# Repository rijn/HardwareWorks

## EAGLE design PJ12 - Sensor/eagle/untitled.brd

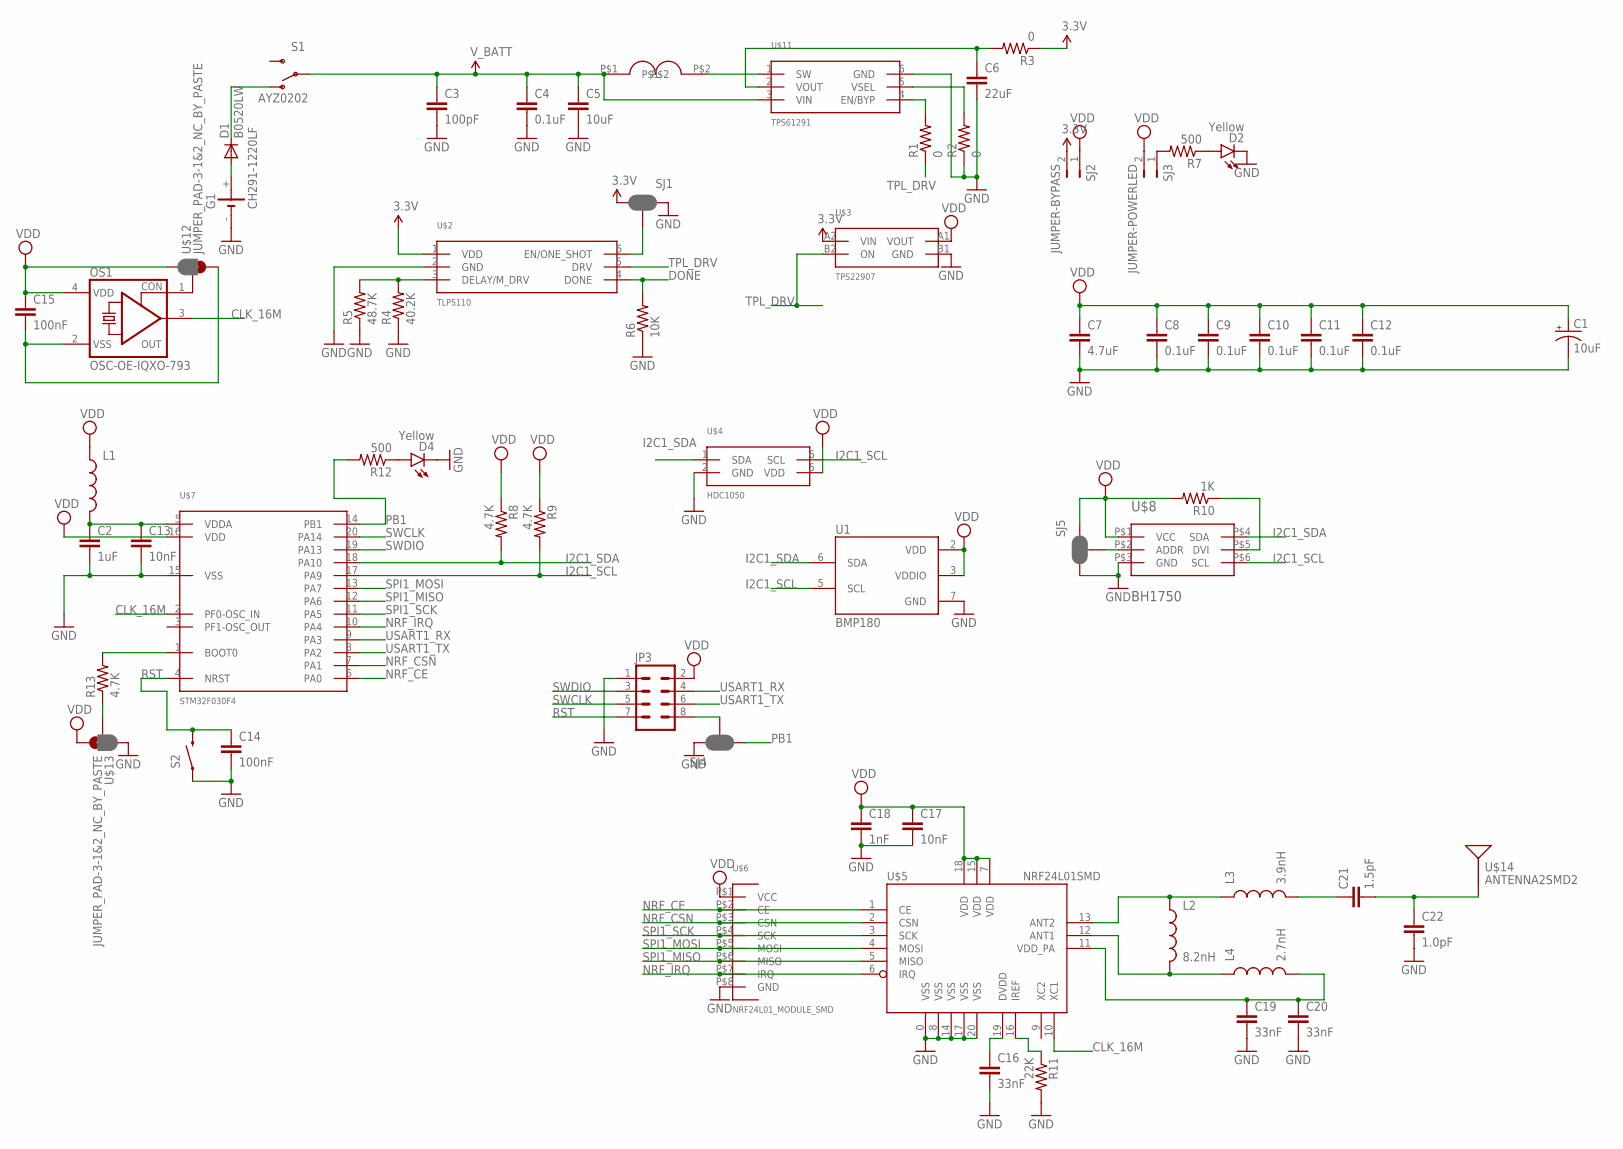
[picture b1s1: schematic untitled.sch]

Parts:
C1: 10uF; EIA3216
C2: 1uF; 0603-CAP
C3: 100pF; 0603-CAP
C4, C8, C9, C10, C11, C12: 0.1uF; 0603-CAP
C5: 10uF; 0603-CAP
C6: 22uF; 0603-CAP
C7: 4.7uF; 0603-CAP
C13, C17: 10nF; 0603-CAP
C14, C15: 100nF; 0603-CAP
C16, C19, C20: 33nF; 0603-CAP
C18: 1nF; 0603-CAP
C21: 1.5pF; 0603-CAP
C22: 1.0pF; 0603-CAP
D1: B0520LW; SOD-123_MINI-SMA
D2, D4: Yellow; LED-0603
G1: CH291-1220LF
JP3: M04X2SMD; 2X4_SMD
L1: INDUCTOR0603; 0603
L2: 8.2nH; 0603
L3: 3.9nH; 0603
L4: 2.7nH; 0603
OS1: OSC-OE-IQXO-793; 2.5X2-4-PAD
R1, R2, R3: 0; 0603
R4: 40.2K; 0805
R5: 48.7K; 0805
R6: 10K; 0603
R7, R12: 500; 0603
R8, R9, R13: 4.7K; 0603
R10: 1K; 0603
R11: 22K; 0603
S1: AYZ0202
S2: SWITCH-MOMENTARY-2SMD-REDUNDANT; TACTILE-SWITCH-SMD
SJ1, SJ4, SJ5: JUMPER-PAD-3-NC_BY_PASTE; PAD-JUMPER-3-NC_BY_PASTE_YES_SILK_FULL_BOX
SJ2: JUMPER-BYPASS; PTH-JUMPER-2-NO_NO_SILK
SJ3: JUMPER-POWERLED; PTH-JUMPER-2-NO_NO_SILK
U1: BMP180
U$1: SWPA4018S3R3MT; SWPA4018S
U$2: TLP5110; DDC(R-PDSO-G6)
U$3: TPS22907; YZT(S-XBGA-N4)
U$4: HDC1050; DMB(S-PWSON-N6)
U$5: NRF24L01SMD; QFN20
U$6: NRF24L01_MODULE_SMD; M08-1.27
U$7: STM32F030F4; TSSOP20
U$8: BH1750; WSOF-6
U$11: TPS61291; DRV(S-PWSON-N6)
U$12, U$13: JUMPER_PAD-3-1&2_NC_BY_PASTE; PAD-HUMPER-3-1&2_NC_BY_PASTE_YES_SILK_FULL_BOX
U$14: ANTENNA2SMD2; ANTENNA-CHIP3

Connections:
3.3V: R3.1, SJ1.1, SJ2.2, U$2.1 (VDD), U$3.A2 (VIN)
CLK_16M: OS1.3 (OUT), U$5.10 (XC1), U$7.2 (PF0-OSC_IN)
DONE: R6.2, U$2.4 (DONE)
GND: C1.C (-), C2.2, C3.2, C4.2, C5.2, C6.2, C7.2, C8.2, C9.2, C10.2, C11.2, C12.2, C13.2, C14.2, C16.2, C17.2, C18.2, C19.2, C20.2, C22.2, D2.C, D4.C, G1.-, JP3.1, R2.1, R4.1, R5.1, R6.1, R11.2, S2.1, S2.2 (1), SJ1.3, SJ4.3, SJ5.1, U1.7 (GND), U$2.2 (GND), U$3.B1 (GND), U$4.2 (GND), U$5.0 (VSS), U$5.8 (VSS), U$5.14 (VSS), U$5.17 (VSS), U$5.20 (VSS), U$6.P$8 (GND), U$7.15 (VSS), U$8.P$3 (GND), U$11.6 (GND), U$13.1
I2C1_SCL: R9.2, U1.5 (SCL), U$4.6 (SCL), U$7.17 (PA9), U$8.P$6 (SCL)
I2C1_SDA: R8.2, U1.6 (SDA), U$4.1 (SDA), U$7.18 (PA10), U$8.P$4 (SDA)
MESH: C1.A (+), C7.1, C8.1, C9.1, C10.1, C11.1, C12.1, R8.1, R9.1, R10.2, SJ2.1, SJ3.2, SJ5.3, U1.2 (VDD), U1.3 (VDDIO), U$6.P$1 (VCC), U$8.P$1 (VCC)
unnamed: D1.A, G1.+
unnamed: D1.C, S1.1 (O)
unnamed: U$1.P$2, U$11.1 (SW)
unnamed: C6.1, R3.2, U$11.2 (VOUT)
unnamed: R1.2, U$11.4 (EN/BYP)
unnamed: R2.2, U$11.5 (VSEL)
unnamed: R4.2, R5.2, U$2.3 (DELAY/M_DRV)
unnamed: R7.2, SJ3.1
unnamed: D2.A, R7.1
unnamed: SJ1.2, U$2.6 (EN/ONE_SHOT)
unnamed: L2.1, L3.1, U$5.13 (ANT2)
unnamed: SJ5.2, U$8.P$2 (ADDR)
unnamed: R10.1, U$8.P$5 (DVI)
unnamed: L2.2, L4.1, U$5.12 (ANT1)
unnamed: D4.A, R12.1
unnamed: C15.2, OS1.2 (VSS), U$12.3
unnamed: C2.1, C13.1, L1.2, U$7.5 (VDDA)
unnamed: C19.1, C20.1, L4.2, U$5.11 (VDD_PA)
unnamed: R13.1, U$13.2
unnamed: JP3.8, SJ4.2
unnamed: R13.2, U$7.1 (BOOT0)
unnamed: OS1.1 (CON), U$12.2
unnamed: C16.1, U$5.19 (DVDD)
unnamed: R11.1, U$5.16 (IREF)
unnamed: C21.1, L3.2
unnamed: C21.2, C22.1, U$14.FEED
NRF_CE: U$5.1 (CE), U$6.P$2 (CE), U$7.6 (PA0)
NRF_CSN: U$5.2 (CSN), U$6.P$3 (CSN), U$7.7 (PA1)
NRF_IRQ: U$5.6 (IRQ), U$6.P$7 (IRQ), U$7.10 (PA4)
PB1: R12.2, SJ4.1, U$7.14 (PB1)
RST: C14.1, JP3.7, S2.3 (2), S2.4 (2), U$7.4 (NRST)
SPI1_MISO: U$5.5 (MISO), U$6.P$6 (MISO), U$7.12 (PA6)
SPI1_MOSI: U$5.4 (MOSI), U$6.P$5 (MOSI), U$7.13 (PA7)
SPI1_SCK: U$5.3 (SCK), U$6.P$4 (SCK), U$7.11 (PA5)
SWCLK: JP3.5, U$7.20 (PA14)
SWDIO: JP3.3, U$7.19 (PA13)
TPL_DRV: R1.1, U$2.5 (DRV), U$3.B2 (ON)
USART1_RX: JP3.4, U$7.9 (PA3)
USART1_TX: JP3.6, U$7.8 (PA2)
VDD: C15.1, C17.1, C18.1, JP3.2, L1.1, OS1.4 (VDD), U$3.A1 (VOUT), U$4.5 (VDD), U$5.7 (VDD), U$5.15 (VDD), U$5.18 (VDD), U$7.16 (VDD), U$12.1, U$13.3
V_BATT: C3.1, C4.1, C5.1, S1.2, U$1.P$1, U$11.3 (VIN)

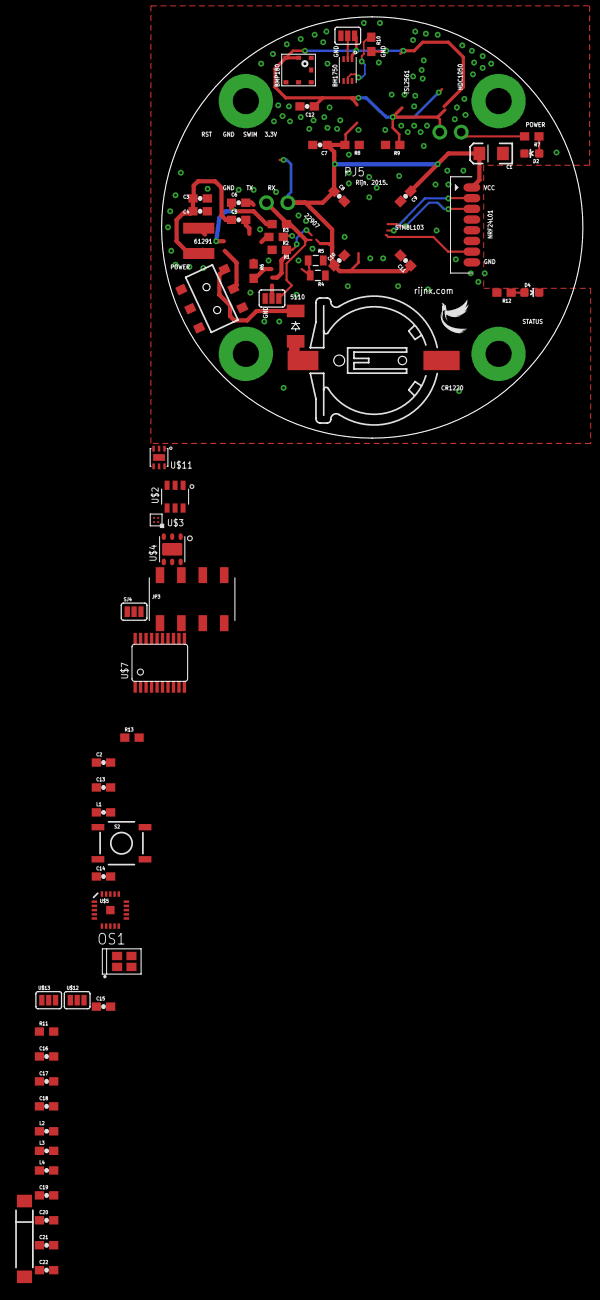
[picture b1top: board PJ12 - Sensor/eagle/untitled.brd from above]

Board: 2 copper layers, 50.0 x 50.0 mm, 67 parts (1 on the bottom side), 48 nets.

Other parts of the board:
U$9: LOGO-3
U$10: LOGO-1

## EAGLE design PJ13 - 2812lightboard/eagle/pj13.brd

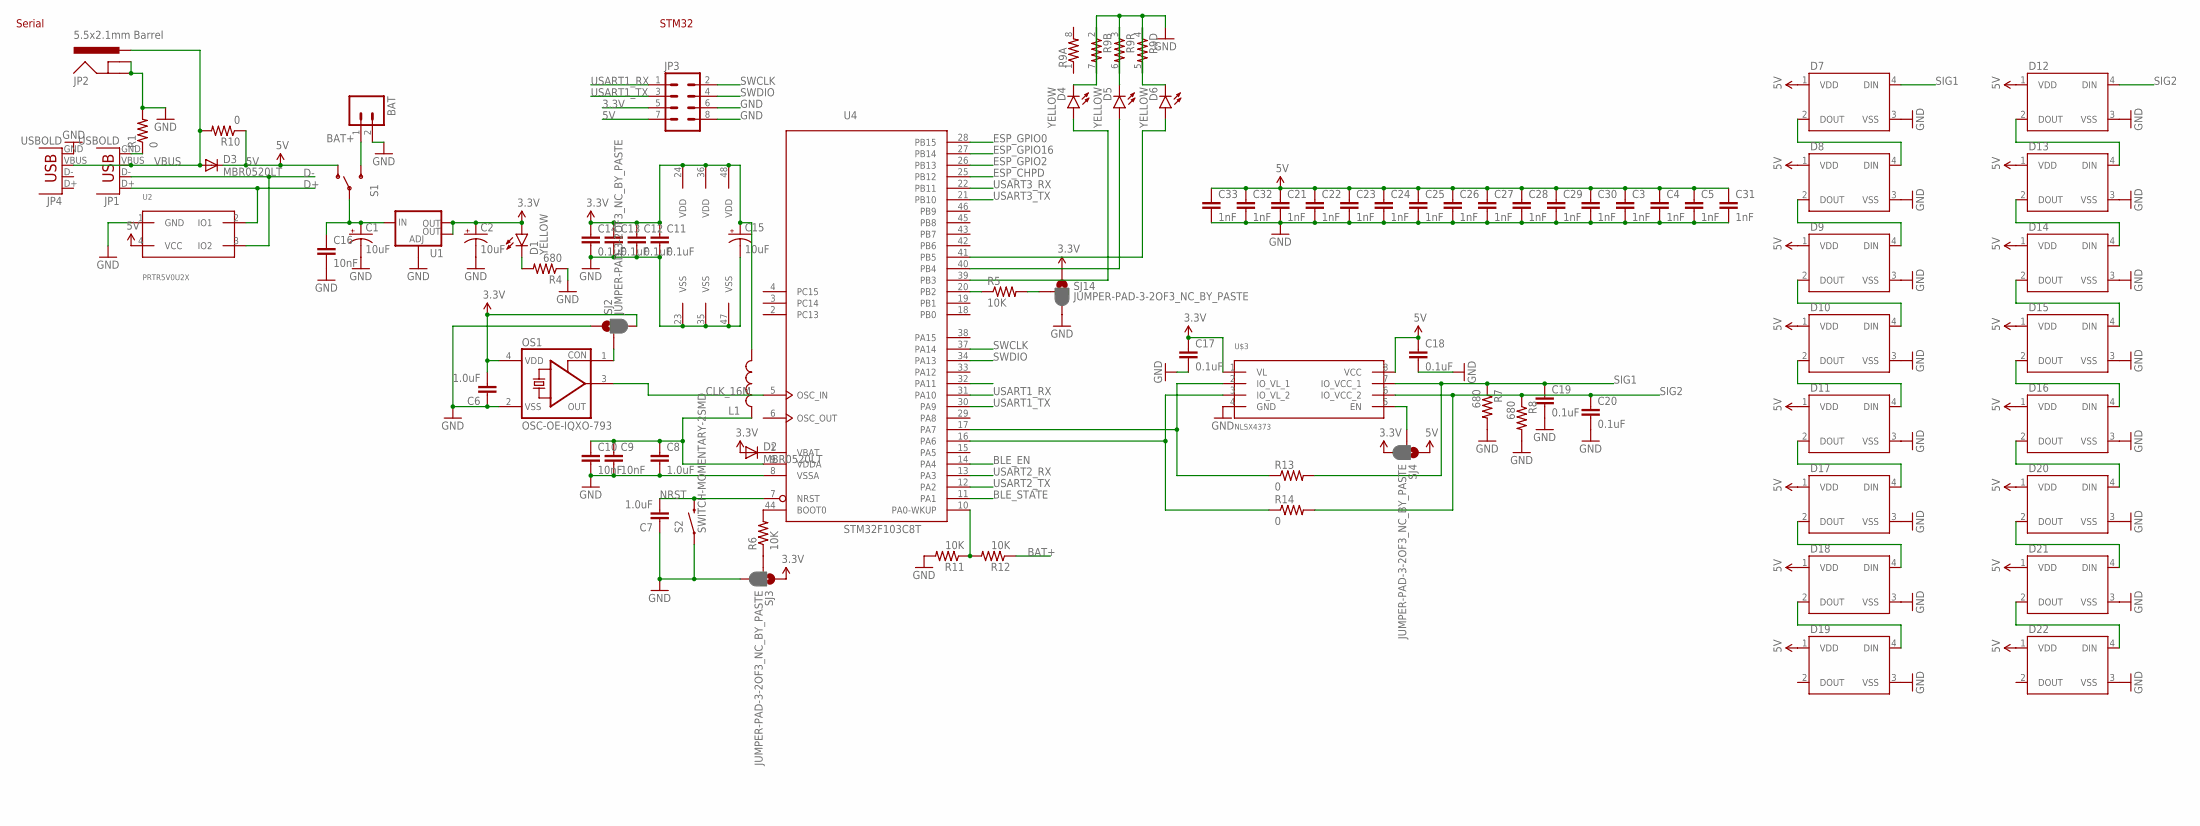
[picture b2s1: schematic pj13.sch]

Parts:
BAT: M02LOCK; 1X02_LOCK
C1, C2, C15: 10uF; EIA3216
C3, C4, C5, C21, C22, C23, C24, C25, C26, C27, C28, C29, C30, C31, C32, C33: 1nF; 0603-CAP
C6, C7, C8: 1.0uF; 0603-CAP
C9, C10, C16: 10nF; 0603-CAP
C11, C12, C13, C14, C17, C18, C19, C20: 0.1uF; 0603-CAP
D1, D4, D5, D6: YELLOW; LED-1206
D2, D3: MBR0520LT; SOD123
D7, D8, D9, D10, D11, D12, D13, D14, D15, D16, D17, D18, D19, D20, D21, D22: WS2812B
JP1, JP4: USBOLD; USB-MINIB-OLD
JP2: 5.5x2.1mm Barrel; POWER_JACK_SMD
JP3: M04X2SMD; 2X4_SMD
L1: INDUCTOR0603; 0603
OS1: OSC-OE-IQXO-793; 2.5X2-4-PAD
R1, R10: 0; 0603
R4, R7, R8: 680; 0603-RES
R5, R6, R11, R12: 10K; 0603-RES
R9: RESISTOR-ARRAY0603-ARV; 0603-ARV
R13, R14: 0; 0603-RES
S1: SWITCH-SPDTSMD; AYZ0202
S2: SWITCH-MOMENTARY-2SMD; TACTILE-SWITCH-SMD
SJ2, SJ3, SJ4, SJ14: JUMPER-PAD-3-2OF3_NC_BY_PASTE; PAD-JUMPER-3-2OF3_NC_BY_PASTE_YES_SILK_FULL_BOX
U1: V_REG_LM1117SOT223; SOT223
U2: PRTR5V0U2X; SOT143
U4: STM32F103C8T; LQFP48
U$3: NLSX4373; SO08

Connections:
3.3V: C2.A (+), C6.2, C11.1, C12.1, C13.1, C14.1, C15.A (+), C17.1, D1.A, D2.A, JP3.5, L1.2, OS1.4 (VDD), SJ2.3, SJ3.1, SJ4.3, SJ14.1, U1.2 (OUT), U1.4 (OUT), U4.24 (VDD), U4.36 (VDD), U4.48 (VDD), U$3.1 (VL)
5V: C3.1, C4.1, C5.1, C18.1, C21.1, C22.1, C23.1, C24.1, C25.1, C26.1, C27.1, C28.1, C29.1, C30.1, C31.1, C32.1, C33.1, D3.C, D7.1 (VDD), D8.1 (VDD), D9.1 (VDD), D10.1 (VDD), D11.1 (VDD), D12.1 (VDD), D13.1 (VDD), D14.1 (VDD), D15.1 (VDD), D16.1 (VDD), D17.1 (VDD), D18.1 (VDD), D19.1 (VDD), D20.1 (VDD), D21.1 (VDD), D22.1 (VDD), JP3.7, R10.1, S1.1 (O), SJ4.1, U2.4 (VCC), U$3.8 (VCC)
BAT+: BAT.1, R12.1, S1.3 (S)
BLE_EN: U4.14 (PA4)
BLE_STATE: U4.11 (PA1)
CLK_16M: OS1.3 (OUT), U4.5 (OSC_IN)
D+: JP1.D+, U2.2 (IO1)
D-: JP1.D-, U2.3 (IO2)
ESP_CHPD: U4.25 (PB12)
ESP_GPIO0: U4.28 (PB15)
ESP_GPIO2: U4.26 (PB13)
ESP_GPIO16: U4.27 (PB14)
GND: BAT.2, C1.C (-), C2.C (-), C3.2, C4.2, C5.2, C6.1, C7.1, C8.2, C9.2, C10.2, C11.2, C12.2, C13.2, C14.2, C15.C (-), C16.2, C17.2, C18.2, C19.2, C20.2, C21.2, C22.2, C23.2, C24.2, C25.2, C26.2, C27.2, C28.2, C29.2, C30.2, C31.2, C32.2, C33.2, D7.3 (VSS), D8.3 (VSS), D9.3 (VSS), D10.3 (VSS), D11.3 (VSS), D12.3 (VSS), D13.3 (VSS), D14.3 (VSS), D15.3 (VSS), D16.3 (VSS), D17.3 (VSS), D18.3 (VSS), D19.3 (VSS), D20.3 (VSS), D21.3 (VSS), D22.3 (VSS), JP2.GND (GNDBREAK), JP2.P$4 (GND), JP3.6, JP3.8, JP4.GND, OS1.2 (VSS), R1.2, R4.1, R7.2, R8.2, R9.5 (2), R9.6 (2), R9.7 (2), R11.2, S2.1, SJ2.1, SJ3.3, SJ14.3, U1.1 (ADJ), U2.1 (GND), U4.8 (VSSA), U4.23 (VSS), U4.35 (VSS), U4.47 (VSS), U$3.4 (GND)
unnamed: JP1.GND, R1.1
unnamed: D11.2 (DOUT), D17.4 (DIN)
unnamed: D1.C, R4.2
unnamed: D2.C, U4.1 (VBAT)
unnamed: R11.1, R12.2, U4.10 (PA0-WKUP)
unnamed: C8.1, C9.1, C10.1, L1.1, U4.9 (VDDA)
unnamed: R6.2, U4.44 (BOOT0)
unnamed: D6.A, U4.41 (PB5)
unnamed: R6.1, SJ3.2
unnamed: D17.2 (DOUT), D18.4 (DIN)
unnamed: OS1.1 (CON), SJ2.2
unnamed: D5.A, U4.40 (PB4)
unnamed: SJ4.2, U$3.5 (EN)
unnamed: D18.2 (DOUT), D19.4 (DIN)
unnamed: D4.A, U4.39 (PB3)
unnamed: D4.C, R9.2 (1)
unnamed: D5.C, R9.3 (1)
unnamed: D6.C, R9.4 (1)
unnamed: C1.A (+), C16.1, S1.2, U1.3 (IN)
unnamed: D12.2 (DOUT), D13.4 (DIN)
unnamed: D13.2 (DOUT), D14.4 (DIN)
unnamed: R13.1, U4.17 (PA7), U$3.2 (IO_VL_1)
unnamed: R14.1, U4.16 (PA6), U$3.3 (IO_VL_2)
unnamed: D7.2 (DOUT), D8.4 (DIN)
unnamed: D8.2 (DOUT), D9.4 (DIN)
unnamed: D9.2 (DOUT), D10.4 (DIN)
unnamed: D10.2 (DOUT), D11.4 (DIN)
unnamed: D14.2 (DOUT), D15.4 (DIN)
unnamed: D15.2 (DOUT), D16.4 (DIN)
unnamed: D16.2 (DOUT), D20.4 (DIN)
unnamed: D20.2 (DOUT), D21.4 (DIN)
unnamed: D21.2 (DOUT), D22.4 (DIN)
unnamed: R5.2, SJ14.2
NRF_CSN: U4.32 (PA11)
NRST: C7.2, S2.3 (2), U4.7 (NRST)
OURET: R5.1, U4.20 (PB2)
SIG1: C19.1, D7.4 (DIN), R7.1, R13.2, U$3.7 (IO_VCC_1)
SIG2: C20.1, D12.4 (DIN), R8.1, R14.2, U$3.6 (IO_VCC_2)
SWCLK: JP3.2, U4.37 (PA14)
SWDIO: JP3.4, U4.34 (PA13)
USART1_RX: JP3.1, U4.31 (PA10)
USART1_TX: JP3.3, U4.30 (PA9)
USART2_RX: U4.13 (PA3)
USART2_TX: U4.12 (PA2)
USART3_RX: U4.22 (PB11)
USART3_TX: U4.21 (PB10)
VBUS: D3.A, JP1.VBUS, JP2.VIN0 (PWR), JP4.VBUS, R10.2

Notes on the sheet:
STM32
Serial

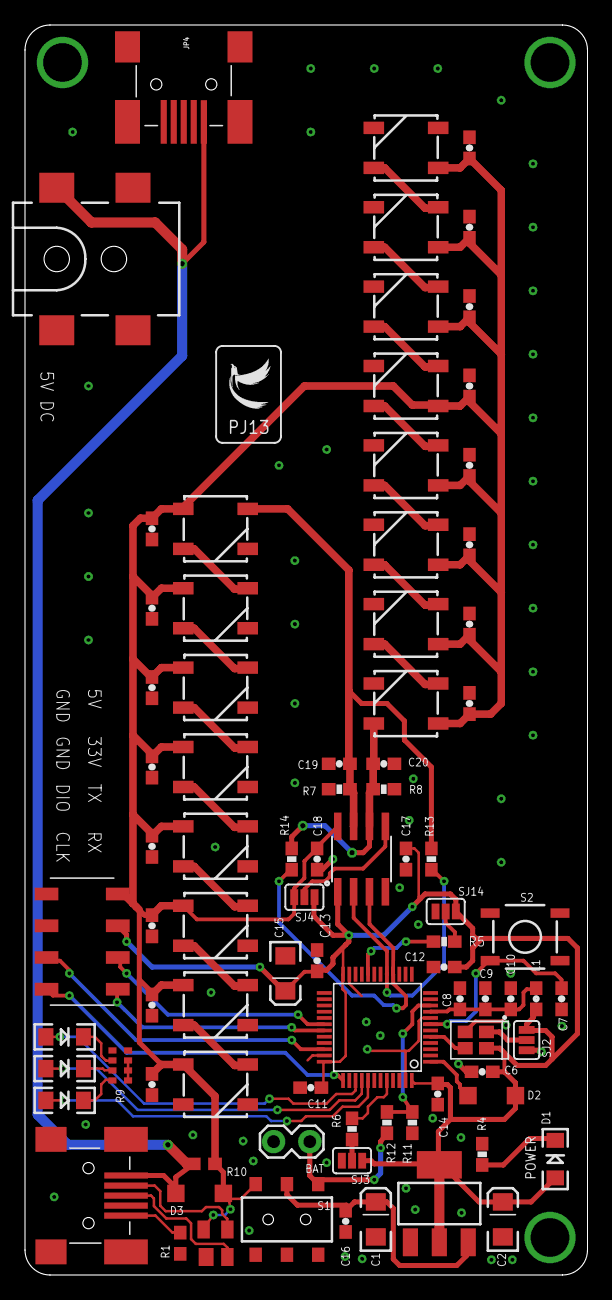
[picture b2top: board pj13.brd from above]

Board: 2 copper layers, 45.0 x 100.0 mm, 86 parts (1 on the bottom side), 49 nets.

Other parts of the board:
U$1: LOGO
U$2: ESD_10.00

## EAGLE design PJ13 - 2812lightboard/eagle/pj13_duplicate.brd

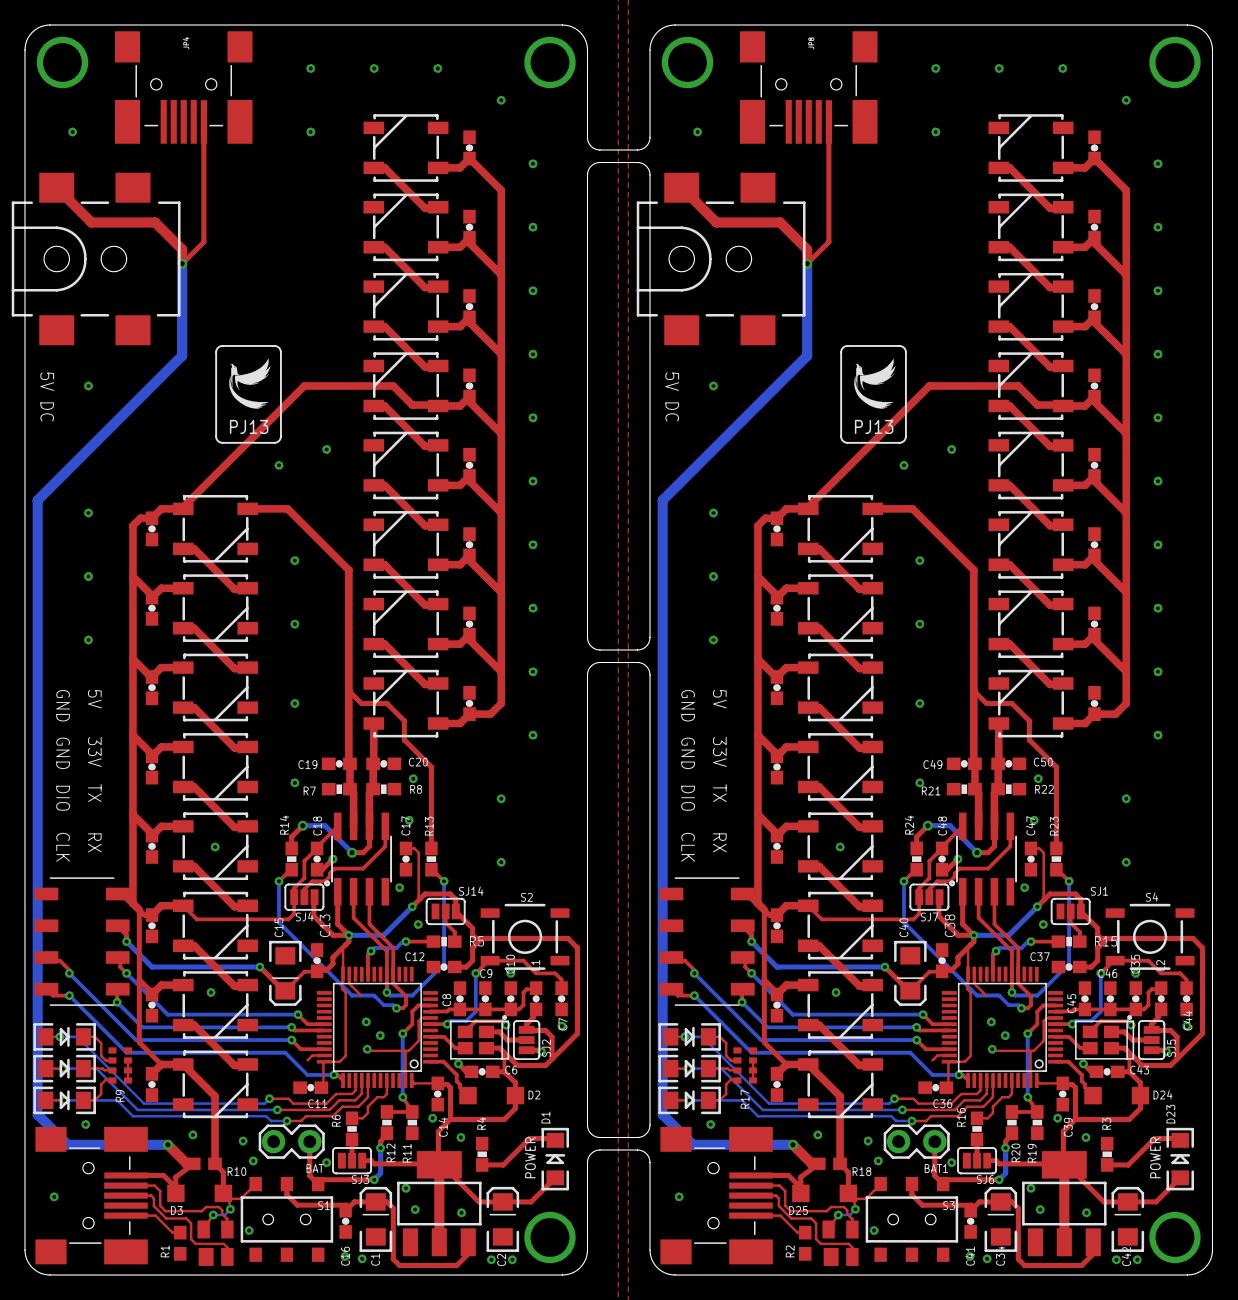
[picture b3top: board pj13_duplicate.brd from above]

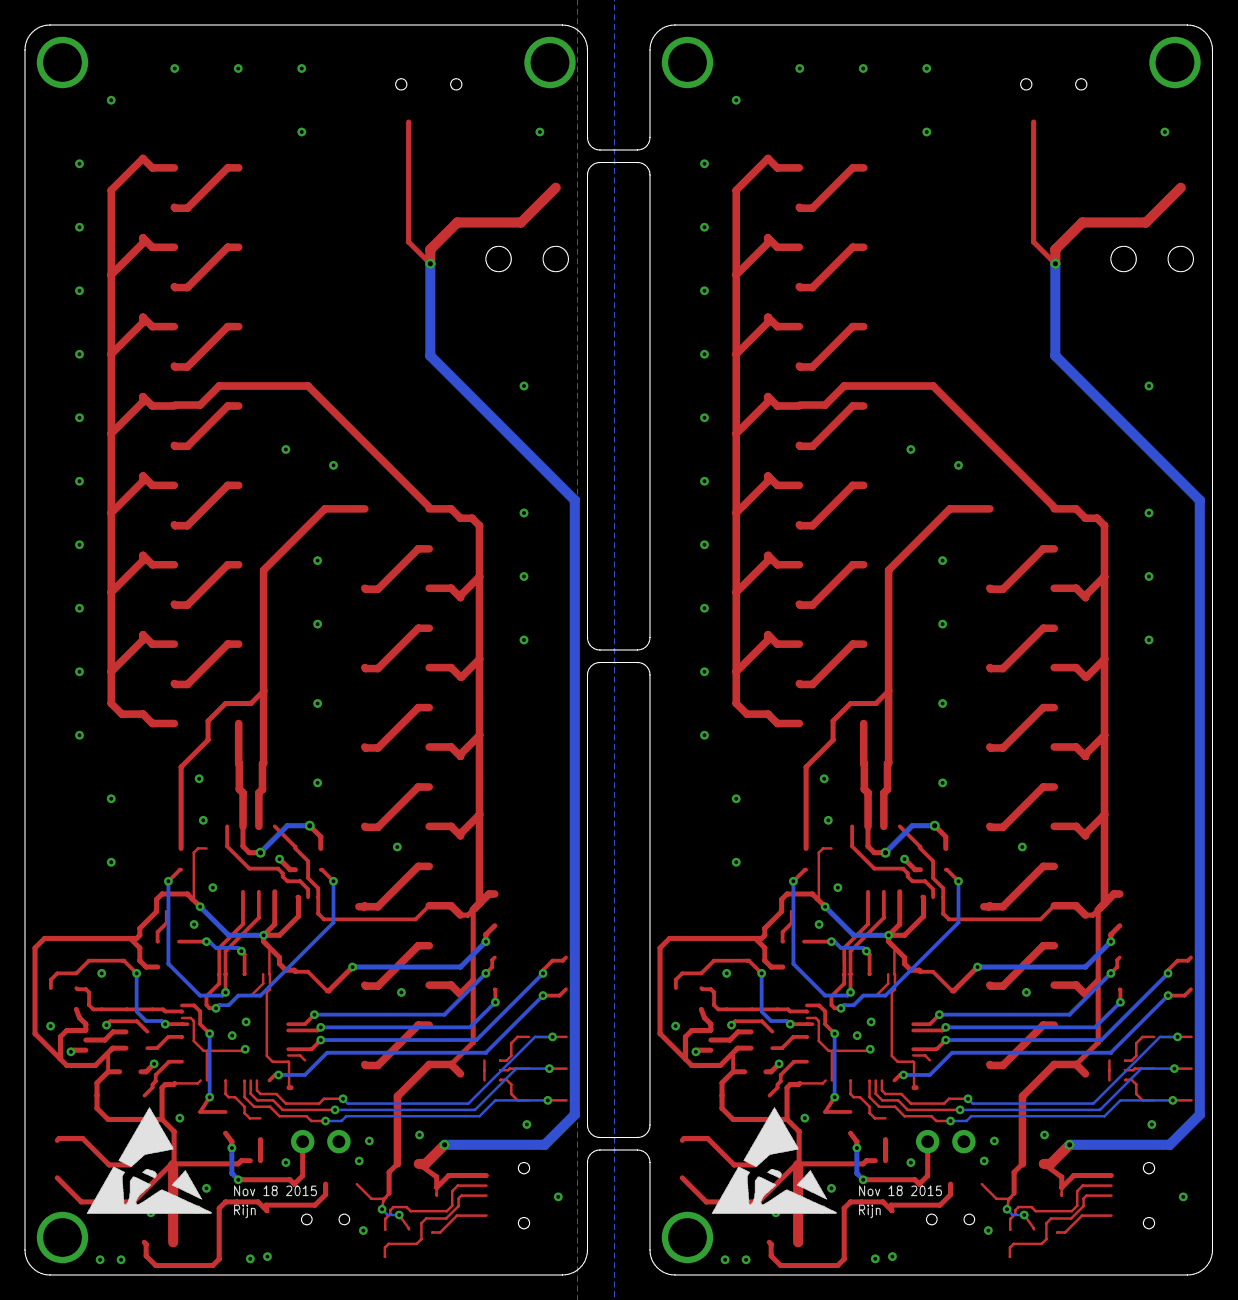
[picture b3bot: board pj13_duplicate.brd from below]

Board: 2 copper layers, 95.0 x 100.0 mm, 172 parts (2 on the bottom side), 98 nets.

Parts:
BAT, BAT1: 1X02_LOCK
C1, C2, C15, C34, C40, C42: 10uF; EIA3216
C3, C4, C5, C21, C22, C23, C24, C25, C26, C27, C28, C29, C30, C31, C32, C33, C51, C52, C53, C54, C55, C56, C57, C58, C59, C60, C61, C62, C63, C64, C65, C66: 1nF; 0603-CAP
C6, C7, C8, C43, C44, C45: 1.0uF; 0603-CAP
C9, C10, C16, C35, C41, C46: 10nF; 0603-CAP
C11, C12, C13, C14, C17, C18, C19, C20, C36, C37, C38, C39, C47, C48, C49, C50: 0.1uF; 0603-CAP
D1, D4, D5, D6, D23, D26, D27, D28: YELLOW; LED-1206
D2, D3, D24, D25: MBR0520LT; SOD123
D7, D8, D9, D10, D11, D12, D13, D14, D15, D16, D17, D18, D19, D20, D21, D22, D29, D30, D31, D32, D33, D34, D35, D36, D37, D38, D39, D40, D41, D42, D43, D44: WS2812B
JP1, JP4, JP5, JP8: USBOLD; USB-MINIB-OLD
JP2, JP7: 5.5x2.1mm Barrel; POWER_JACK_SMD
JP3, JP6: 2X4_SMD
L1, L2: 0603
OS1, OS2: OSC-OE-IQXO-793; 2.5X2-4-PAD
R1, R2, R10, R18: 0; 0603
R3, R4, R7, R8, R21, R22: 680; 0603-RES
R5, R6, R11, R12, R15, R16, R19, R20: 10K; 0603-RES
R9, R17: 0603-ARV
R13, R14, R23, R24: 0; 0603-RES
S1, S3: AYZ0202
S2, S4: SWITCH-MOMENTARY-2SMD; TACTILE-SWITCH-SMD
SJ1, SJ2, SJ3, SJ4, SJ5, SJ6, SJ7, SJ14: JUMPER-PAD-3-2OF3_NC_BY_PASTE; PAD-JUMPER-3-2OF3_NC_BY_PASTE_YES_SILK_FULL_BOX
U1, U3: SOT223
U2, U5: PRTR5V0U2X; SOT143
U4, U6: STM32F103C8T; LQFP48
U$1, U$4: LOGO
U$2, U$5: ESD_10.00
U$3, U$6: NLSX4373; SO08

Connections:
3.3V: C2.A, C6.2, C11.1, C12.1, C13.1, C14.1, C15.A, C17.1, D1.A, D2.A, JP3.5, L1.2, OS1.4, SJ2.3, SJ3.1, SJ4.3, SJ14.1, U1.2, U1.4, U4.24, U4.36, U4.48, U$3.1
3.3V1: C36.1, C37.1, C38.1, C39.1, C40.A, C42.A, C43.2, C47.1, D23.A, D24.A, JP6.5, L2.2, OS2.4, SJ1.1, SJ5.3, SJ6.1, SJ7.3, U3.2, U3.4, U6.24, U6.36, U6.48, U$6.1
5V: C3.1, C4.1, C5.1, C18.1, C21.1, C22.1, C23.1, C24.1, C25.1, C26.1, C27.1, C28.1, C29.1, C30.1, C31.1, C32.1, C33.1, D3.C, D7.1, D8.1, D9.1, D10.1, D11.1, D12.1, D13.1, D14.1, D15.1, D16.1, D17.1, D18.1, D19.1, D20.1, D21.1, D22.1, JP3.7, R10.1, S1.1, SJ4.1, U2.4, U$3.8
5V1: C48.1, C51.1, C52.1, C53.1, C54.1, C55.1, C56.1, C57.1, C58.1, C59.1, C60.1, C61.1, C62.1, C63.1, C64.1, C65.1, C66.1, D25.C, D29.1, D30.1, D31.1, D32.1, D33.1, D34.1, D35.1, D36.1, D37.1, D38.1, D39.1, D40.1, D41.1, D42.1, D43.1, D44.1, JP6.7, R18.1, S3.1, SJ7.1, U5.4, U$6.8
BAT+: BAT.1, R12.1, S1.3
BAT+1: BAT1.1, R20.1, S3.3
CLK_16M: OS1.3, U4.5
CLK_16M1: OS2.3, U6.5
D+: JP1.D+, U2.2
D+1: JP5.D+, U5.2
D-: JP1.D-, U2.3
D-1: JP5.D-, U5.3
GND: BAT.2, C1.C, C2.C, C3.2, C4.2, C5.2, C6.1, C7.1, C8.2, C9.2, C10.2, C11.2, C12.2, C13.2, C14.2, C15.C, C16.2, C17.2, C18.2, C19.2, C20.2, C21.2, C22.2, C23.2, C24.2, C25.2, C26.2, C27.2, C28.2, C29.2, C30.2, C31.2, C32.2, C33.2, D7.3, D8.3, D9.3, D10.3, D11.3, D12.3, D13.3, D14.3, D15.3, D16.3, D17.3, D18.3, D19.3, D20.3, D21.3, D22.3, JP2.GND, JP2.P$4, JP3.6, JP3.8, JP4.GND, OS1.2, R1.2, R4.1, R7.2, R8.2, R9.5, R9.6, R9.7, R11.2, S2.1, SJ2.1, SJ3.3, SJ14.3, U1.1, U2.1, U4.8, U4.23, U4.35, U4.47, U$3.4
GND1: BAT1.2, C34.C, C35.2, C36.2, C37.2, C38.2, C39.2, C40.C, C41.2, C42.C, C43.1, C44.1, C45.2, C46.2, C47.2, C48.2, C49.2, C50.2, C51.2, C52.2, C53.2, C54.2, C55.2, C56.2, C57.2, C58.2, C59.2, C60.2, C61.2, C62.2, C63.2, C64.2, C65.2, C66.2, D29.3, D30.3, D31.3, D32.3, D33.3, D34.3, D35.3, D36.3, D37.3, D38.3, D39.3, D40.3, D41.3, D42.3, D43.3, D44.3, JP6.6, JP6.8, JP7.GND, JP7.P$4, JP8.GND, OS2.2, R2.2, R3.1, R17.5, R17.6, R17.7, R19.2, R21.2, R22.2, S4.1, SJ1.3, SJ5.1, SJ6.3, U3.1, U5.1, U6.8, U6.23, U6.35, U6.47, U$6.4
unnamed: JP1.GND, R1.1
unnamed: D11.2, D17.4
unnamed: D1.C, R4.2
unnamed: D2.C, U4.1
unnamed: R11.1, R12.2, U4.10
unnamed: C8.1, C9.1, C10.1, L1.1, U4.9
unnamed: R6.2, U4.44
unnamed: D6.A, U4.41
unnamed: R6.1, SJ3.2
unnamed: D17.2, D18.4
unnamed: OS1.1, SJ2.2
unnamed: D5.A, U4.40
unnamed: SJ4.2, U$3.5
unnamed: D18.2, D19.4
unnamed: D4.A, U4.39
unnamed: D4.C, R9.2
unnamed: D5.C, R9.3
unnamed: D6.C, R9.4
unnamed: C1.A, C16.1, S1.2, U1.3
unnamed: D12.2, D13.4
unnamed: D13.2, D14.4
unnamed: R13.1, U4.17, U$3.2
unnamed: R14.1, U4.16, U$3.3
unnamed: D7.2, D8.4
unnamed: D8.2, D9.4
unnamed: D9.2, D10.4
unnamed: D10.2, D11.4
unnamed: D14.2, D15.4
unnamed: D15.2, D16.4
unnamed: D16.2, D20.4
unnamed: D20.2, D21.4
unnamed: D21.2, D22.4
unnamed: JP5.GND, R2.1
unnamed: D23.C, R3.2
unnamed: R16.2, U6.44
unnamed: R16.1, SJ6.2
unnamed: OS2.1, SJ5.2
unnamed: C35.1, C45.1, C46.1, L2.1, U6.9
unnamed: D24.C, U6.1
unnamed: R15.2, SJ1.2
unnamed: D28.A, U6.41
unnamed: D27.A, U6.40
unnamed: D26.A, U6.39
unnamed: R5.2, SJ14.2
unnamed: D26.C, R17.2
unnamed: D27.C, R17.3
unnamed: D28.C, R17.4
unnamed: C34.A, C41.1, S3.2, U3.3
unnamed: R19.1, R20.2, U6.10
unnamed: SJ7.2, U$6.5
unnamed: R23.1, U6.17, U$6.2
unnamed: R24.1, U6.16, U$6.3
unnamed: D29.2, D30.4
unnamed: D30.2, D31.4
unnamed: D31.2, D32.4
unnamed: D32.2, D33.4
unnamed: D34.2, D35.4
unnamed: D35.2, D36.4
unnamed: D36.2, D37.4
unnamed: D37.2, D38.4
unnamed: D33.2, D39.4
unnamed: D39.2, D40.4
unnamed: D40.2, D41.4
unnamed: D38.2, D42.4
unnamed: D42.2, D43.4
unnamed: D43.2, D44.4
NRST: C7.2, S2.3, U4.7
NRST1: C44.2, S4.3, U6.7
OURET: R5.1, U4.20
OURET1: R15.1, U6.20
SIG1: C19.1, D7.4, R7.1, R13.2, U$3.7
SIG2: C20.1, D12.4, R8.1, R14.2, U$3.6
SIG3: C49.1, D29.4, R21.1, R23.2, U$6.7
SIG4: C50.1, D34.4, R22.1, R24.2, U$6.6
SWCLK: JP3.2, U4.37
SWCLK1: JP6.2, U6.37
SWDIO: JP3.4, U4.34
SWDIO1: JP6.4, U6.34
USART1_RX: JP3.1, U4.31
USART1_RX1: JP6.1, U6.31
USART1_TX: JP3.3, U4.30
USART1_TX1: JP6.3, U6.30
VBUS: D3.A, JP1.VBUS, JP2.VIN0, JP4.VBUS, R10.2
VBUS1: D25.A, JP5.VBUS, JP7.VIN0, JP8.VBUS, R18.2

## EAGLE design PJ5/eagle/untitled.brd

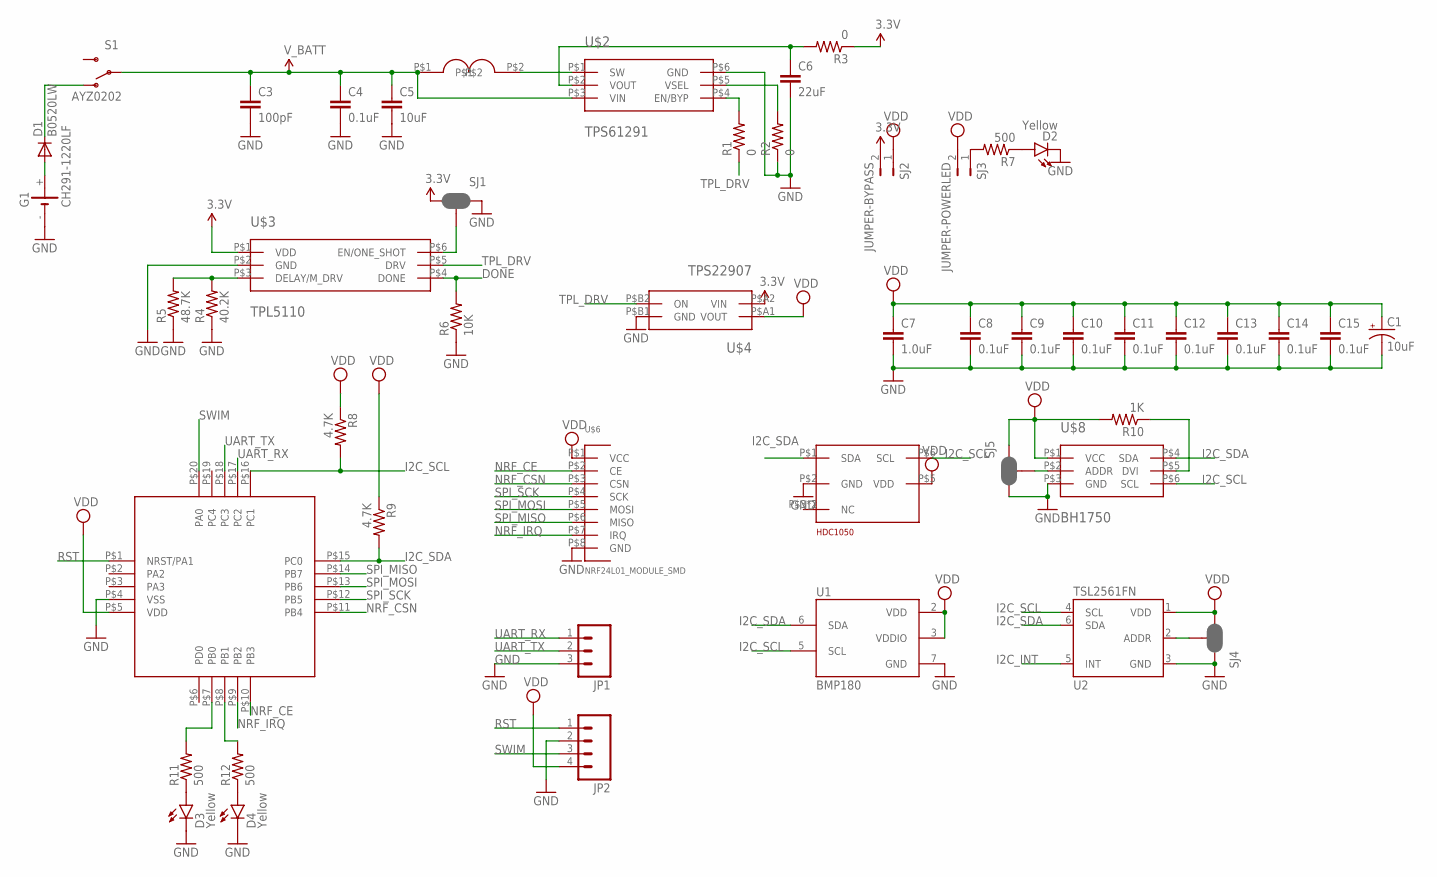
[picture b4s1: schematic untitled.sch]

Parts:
C1: 10uF; EIA3216
C3: 100pF; 0603-CAP
C4, C8, C9, C10, C11, C12, C13, C14, C15: 0.1uF; 0603-CAP
C5: 10uF; 0603-CAP
C6: 22uF; 0603-CAP
C7: 1.0uF; 0603-CAP
D1: B0520LW; SOD-123_MINI-SMA
D2, D3, D4: Yellow; LED-0603
G1: CH291-1220LF
JP1: M03LOCK; 1X03_LOCK
JP2: M04LOCK; 1X04_LOCK
R1, R2, R3: 0; 0603
R4: 40.2K; 0805
R5: 48.7K; 0805
R6: 10K; 0603
R7, R11, R12: 500; 0603
R8, R9: 4.7K; 0603
R10: 1K; 0603
S1: AYZ0202
SJ1, SJ4, SJ5: JUMPER-PAD-3-NC_BY_PASTE; PAD-JUMPER-3-NC_BY_PASTE_YES_SILK_FULL_BOX
SJ2: JUMPER-BYPASS; PTH-JUMPER-2-NO_NO_SILK
SJ3: JUMPER-POWERLED; PTH-JUMPER-2-NO_NO_SILK
U1: BMP180
U2: TSL2561FN; FN-6
U$1: SWPA4018S3R3MT; SWPA4018S
U$2: TPS61291; PWSON-N6
U$3: TPL5110; DDC(R-PDSO-G6)
U$4: TPS22907; YZT(S-XBGA-N4)
U$5: STM8L101; UFQFPN20
U$6: NRF24L01_MODULE_SMD; M08-1.27
U$7: HDC1050; PWSON-N6
U$8: BH1750; WSOF-6

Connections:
3.3V: R3.1, SJ1.1, SJ2.2, U$3.P$1 (VDD), U$4.P$A2 (VIN)
DONE: R6.2, U$3.P$4 (DONE)
GND: C1.C (-), C3.2, C4.2, C5.2, C6.2, C7.2, C8.2, C9.2, C10.2, C11.2, C12.2, C13.2, C14.2, C15.2, D2.C, D3.C, D4.C, G1.-, JP1.3, JP2.2, R2.1, R4.1, R5.1, R6.1, SJ1.3, SJ4.3, SJ5.1, U1.7 (GND), U2.3 (GND), U$2.P$6 (GND), U$3.P$2 (GND), U$4.P$B1 (GND), U$5.P$4 (VSS), U$6.P$8 (GND), U$7.P$2 (GND), U$8.P$3 (GND)
I2C_INT: U2.5 (INT)
I2C_SCL: R8.2, U1.5 (SCL), U2.4 (SCL), U$5.P$16 (PC1), U$7.P$6 (SCL), U$8.P$6 (SCL)
I2C_SDA: R9.2, U1.6 (SDA), U2.6 (SDA), U$5.P$15 (PC0), U$7.P$1 (SDA), U$8.P$4 (SDA)
MESH: C1.A (+), C7.1, C8.1, C9.1, C10.1, C11.1, C12.1, C13.1, C14.1, C15.1, JP2.4, R8.1, R9.1, R10.2, SJ2.1, SJ3.2, SJ4.1, SJ5.3, U1.2 (VDD), U1.3 (VDDIO), U2.1 (VDD), U$4.P$A1 (VOUT), U$5.P$5 (VDD), U$6.P$1 (VCC), U$7.P$5 (VDD), U$8.P$1 (VCC)
unnamed: D1.A, G1.+
unnamed: D1.C, S1.1 (O)
unnamed: U$1.P$2, U$2.P$1 (SW)
unnamed: C6.1, R3.2, U$2.P$2 (VOUT)
unnamed: R1.2, U$2.P$4 (EN/BYP)
unnamed: R2.2, U$2.P$5 (VSEL)
unnamed: R4.2, R5.2, U$3.P$3 (DELAY/M_DRV)
unnamed: R7.2, SJ3.1
unnamed: D2.A, R7.1
unnamed: SJ1.2, U$3.P$6 (EN/ONE_SHOT)
unnamed: SJ4.2, U2.2 (ADDR)
unnamed: SJ5.2, U$8.P$2 (ADDR)
unnamed: R10.1, U$8.P$5 (DVI)
unnamed: D3.A, R11.1
unnamed: D4.A, R12.1
unnamed: R11.2, U$5.P$7 (PB0)
unnamed: R12.2, U$5.P$8 (PB1)
NRF_CE: U$5.P$10 (PB3), U$6.P$2 (CE)
NRF_CSN: U$5.P$11 (PB4), U$6.P$3 (CSN)
NRF_IRQ: U$5.P$9 (PB2), U$6.P$7 (IRQ)
RST: JP2.1, U$5.P$1 (NRST/PA1)
SPI_MISO: U$5.P$14 (PB7), U$6.P$6 (MISO)
SPI_MOSI: U$5.P$13 (PB6), U$6.P$5 (MOSI)
SPI_SCK: U$5.P$12 (PB5), U$6.P$4 (SCK)
SWIM: JP2.3, U$5.P$20 (PA0)
TPL_DRV: R1.1, U$3.P$5 (DRV), U$4.P$B2 (ON)
UART_RX: JP1.1, U$5.P$17 (PC2)
UART_TX: JP1.2, U$5.P$18 (PC3)
V_BATT: C3.1, C4.1, C5.1, S1.2, U$1.P$1, U$2.P$3 (VIN)

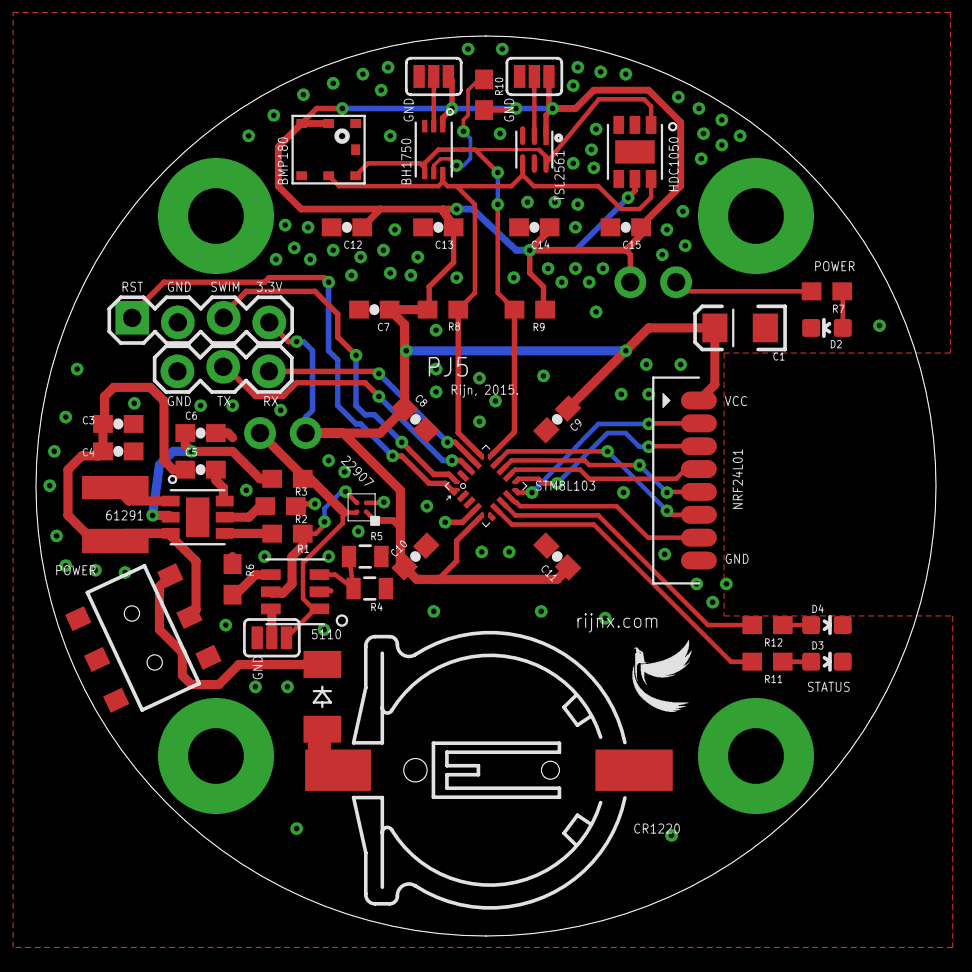
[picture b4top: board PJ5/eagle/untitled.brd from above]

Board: 2 copper layers, 50.0 x 50.0 mm, 51 parts (1 on the bottom side), 35 nets.

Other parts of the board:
U$9: LOGO-3
U$10: LOGO-1

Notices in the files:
parts and their libraries:
SparkFun-Capacitors: Licensing: Creative Commons ShareAlike 4.0 International - https://creativecommons.org/licenses/by-sa/4.0
